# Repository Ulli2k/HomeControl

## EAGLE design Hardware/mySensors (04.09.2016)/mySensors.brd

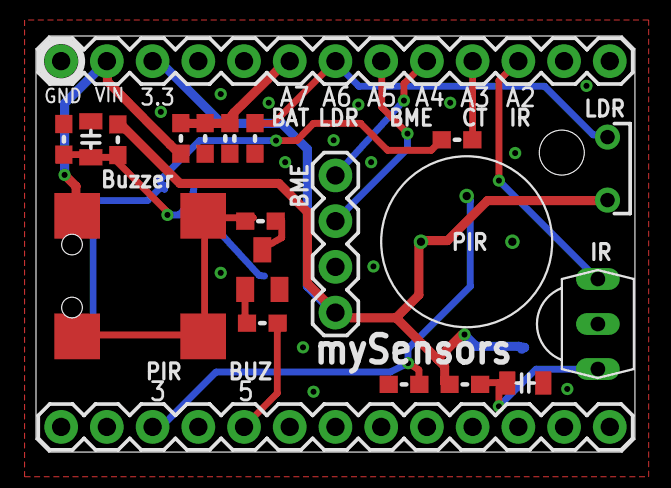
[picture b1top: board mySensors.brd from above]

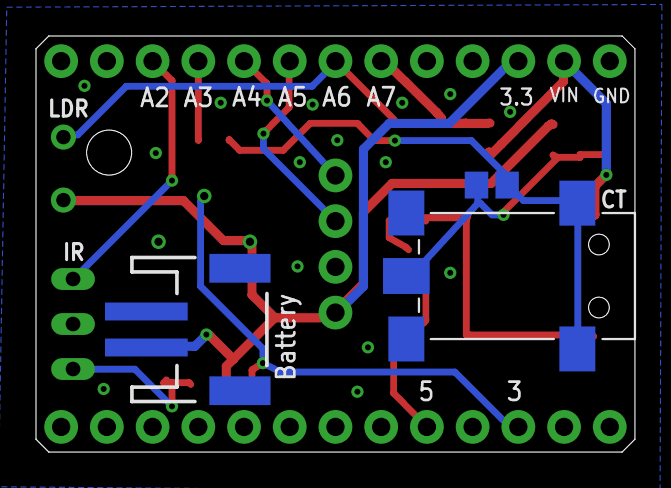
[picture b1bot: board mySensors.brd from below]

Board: 2 copper layers, 33.3 x 23.1 mm, 24 parts (3 on the bottom side), 17 nets.

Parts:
ANALOGSIDE: M13; 1X13
BC817-40: SOT23-BEC
BURDEN: R150 0.1%; R0805
C2: 10u; 0805-CAP
C3: 4,7u; 0805-CAP
C105: 0,1u; 0603-CAP
CT1: 1503_13; 1503-03
DIGITALSIDE: M13; 1X13
IR-RX: TSOP4836; TSOP18XX
J1: JST-2-SMD
JP1: CONNECTORS_M4""; CONNECTORS_1X4
LDR: GL5537; M9960
PIEZO: BUZZER-PIEZO_SMD
R1: 100k; 0603-RES
R2, R5, R104: 470k; 0603-RES
R3: 100; 0603-RES
R4: 33; 0603-RES
R6, R103: 1k; 0603-RES
R7: 1M; 0603-RES
R8: 301k; 0603-RES
U$1: EKMB1X011X; PIR-PANASONIC-VZ-WL-STANDARD

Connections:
+3V3: ANALOGSIDE.11, J1.2, JP1.1, LDR.1, R2.1, R3.2, U$1.VDD
A2_IR-RX: ANALOGSIDE.3, IR-RX.OUT
A3_RFM-3_RST: ANALOGSIDE.4, R6.2
A4_SDA_BME: ANALOGSIDE.5, JP1.4
A5_SCL_BME: ANALOGSIDE.6, JP1.3
A6_LDR: ANALOGSIDE.7, LDR.2, R8.2
A7_BAT-SENS: ANALOGSIDE.8, C105.1, R7.2, R104.1
D3_RFM-2_IRQ: DIGITALSIDE.11, R1.1, U$1.OUT
D5_BUZZER: DIGITALSIDE.9, R103.1
GND: ANALOGSIDE.13, BC817-40.E, C2.2, C3.2, C105.2, IR-RX.GND, J1.1, JP1.2, R1.2, R5.2, R8.1, R104.2, U$1.GND
unnamed: BURDEN.2, C2.1, CT1.1, R2.2, R5.1
unnamed: BURDEN.1, CT1.4, CT1.4-2, R6.1
unnamed: PIEZO.-, PIEZO.DUMMY, PIEZO.DUMMY1, R4.1
unnamed: BC817-40.C, R4.2
unnamed: BC817-40.B, R103.2
unnamed: C3.1, IR-RX.VCC, R3.1
VCC: ANALOGSIDE.12, PIEZO.+, R7.1

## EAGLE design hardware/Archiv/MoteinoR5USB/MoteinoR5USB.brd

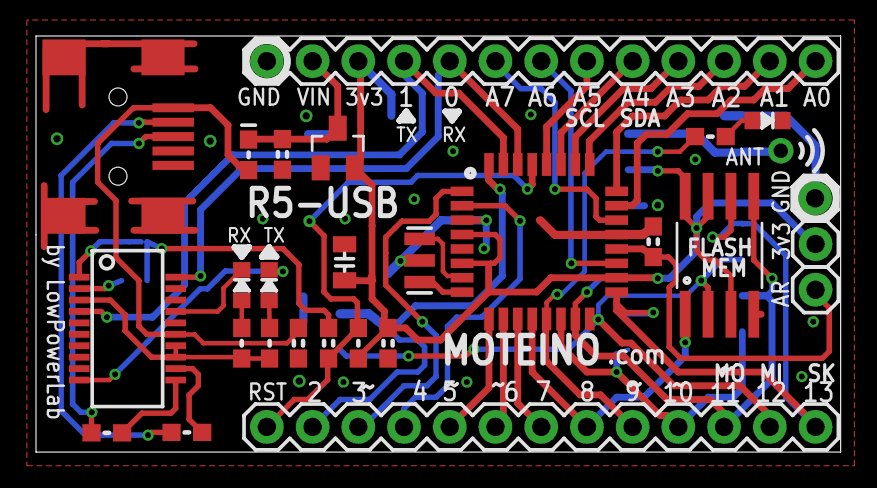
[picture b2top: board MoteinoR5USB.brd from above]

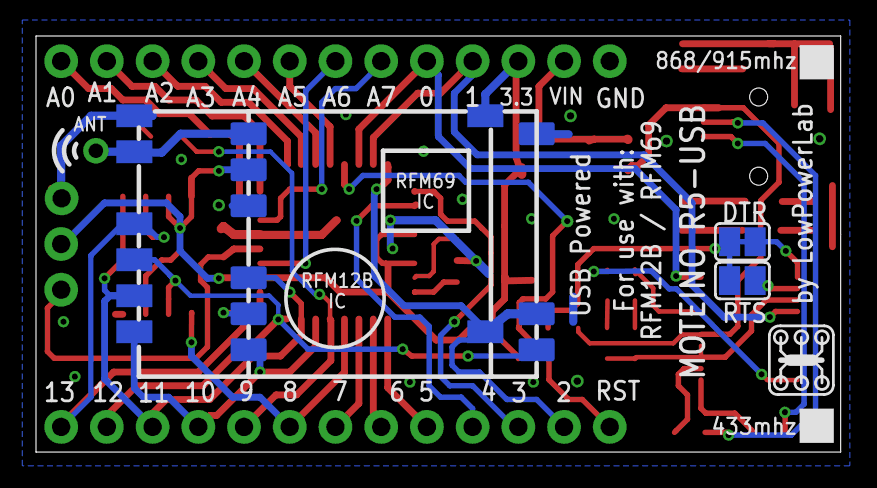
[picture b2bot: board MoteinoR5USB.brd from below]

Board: 2 copper layers, 44.7 x 23.1 mm, 33 parts (5 on the bottom side), 44 nets.

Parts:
+: M01PTH; 1X01
ANALOGSIDE: M13; 1X13
ATMEGA328: ATMega-328; TQFP32-08
C1, C4, C5: 0.1; 0603-CAP
C2: 1u; 0603-CAP
C3: 10u; 0805-CAP
C6: 0.1u; 0603-CAP
CN1: MINIB; USB-MINIB
D: SHOTTKY; 0603-RES
DIGITALSIDE: M13; 1X13
IC3: MCP1703CB; SOT23
JP1, JP2: M01PTH; 1X01
R1: 10k; 0603-RES
R2: 1k5; 0603-RES
R3, R5: 27; 0603-RES
R4, R6: 0603-RES
RFM12B: RFM12B_MINPADS; RFM12B-MINPADS
SJ1, SJ6: SJW
U1: FT231XS; SSOP20_L
U$1: RFM12B_ANTENNA; RFM12B-ANTENNA
U$2, U$4, U$7: LED0603; 0603-LED
U$3: LOGO_LOWPOWERLAB
U$5: RFM69; RFM69W-MINPADS
U$6: AT25F512BWIDE_5.3MM; SO08WIDE
X1: 16 MHz; RESONATOR-SMD

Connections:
A0: ANALOGSIDE.1, ATMEGA328.23
A1: ANALOGSIDE.2, ATMEGA328.24
A2: ANALOGSIDE.3, ATMEGA328.25
A3: ANALOGSIDE.4, ATMEGA328.26
A4_SDA: ANALOGSIDE.5, ATMEGA328.27
A5_SCL: ANALOGSIDE.6, ATMEGA328.28
A6: ANALOGSIDE.7, ATMEGA328.19
A7: ANALOGSIDE.8, ATMEGA328.22
AREF: ATMEGA328.20, C5.1, JP1.1
D0_RX: ANALOGSIDE.9, ATMEGA328.30, U1.20
D1_TX: ANALOGSIDE.10, ATMEGA328.31, U1.4
D2: ATMEGA328.32, DIGITALSIDE.12, RFM12B.IRQ, U$5.DIO0
D3: ATMEGA328.1, DIGITALSIDE.11
D4: ATMEGA328.2, DIGITALSIDE.10
D5: ATMEGA328.9, DIGITALSIDE.9
D6: ATMEGA328.10, DIGITALSIDE.8
D7: ATMEGA328.11, DIGITALSIDE.7
D8: ATMEGA328.12, DIGITALSIDE.6, U$6.1
D9: ATMEGA328.13, DIGITALSIDE.5, R2.2
D10_SS: ATMEGA328.14, DIGITALSIDE.4, RFM12B.SEL, U$5.NSS
D11_MOSI: ATMEGA328.15, DIGITALSIDE.3, RFM12B.SDI, U$5.MOSI, U$6.5
D12_MISO: ATMEGA328.16, DIGITALSIDE.2, RFM12B.SDO, U$5.MISO, U$6.2
D13_SCK: ATMEGA328.17, DIGITALSIDE.1, RFM12B.SCK, U$5.SCK, U$6.6
D+: CN1.D+, R5.1
D-: CN1.D-, R3.1
DTR: SJ6.2, U1.1
FTDI3.3V: R4.2, R6.2, U1.3, U1.13, U1.14
GND: ANALOGSIDE.13, ATMEGA328.3, ATMEGA328.5, ATMEGA328.21, C2.2, C3.2, C4.2, C5.2, C6.2, CN1.GND, IC3.1, JP2.1, RFM12B.GND, U1.6, U1.16, U$2.MINUS, U$5.GND, U$6.4, X1.2
unnamed: ATMEGA328.7, X1.1
unnamed: R2.1, U$2.PLUS
unnamed: RFM12B.ANT, U$1.P$1, U$5.ANA
unnamed: R3.2, U1.12
unnamed: R5.2, U1.11
unnamed: U1.17, U$4.MINUS
unnamed: U1.10, U$7.MINUS
unnamed: R4.1, U$7.PLUS
unnamed: R6.1, U$4.PLUS
unnamed: ATMEGA328.8, X1.3
RST: ATMEGA328.29, C1.1, DIGITALSIDE.13, R1.2
RTS: SJ1.1, U1.2
RTS_OR_DTR: C1.2, SJ1.2, SJ6.1
VBUS: C6.1, CN1.VBUS, D.2, U1.15
VCC: +.1, ANALOGSIDE.11, ATMEGA328.4, ATMEGA328.6, ATMEGA328.18, C3.1, C4.1, IC3.2, R1.1, RFM12B.VDD, U$5.VDD, U$6.3, U$6.7, U$6.8
VIN: ANALOGSIDE.12, C2.1, D.1, IC3.3

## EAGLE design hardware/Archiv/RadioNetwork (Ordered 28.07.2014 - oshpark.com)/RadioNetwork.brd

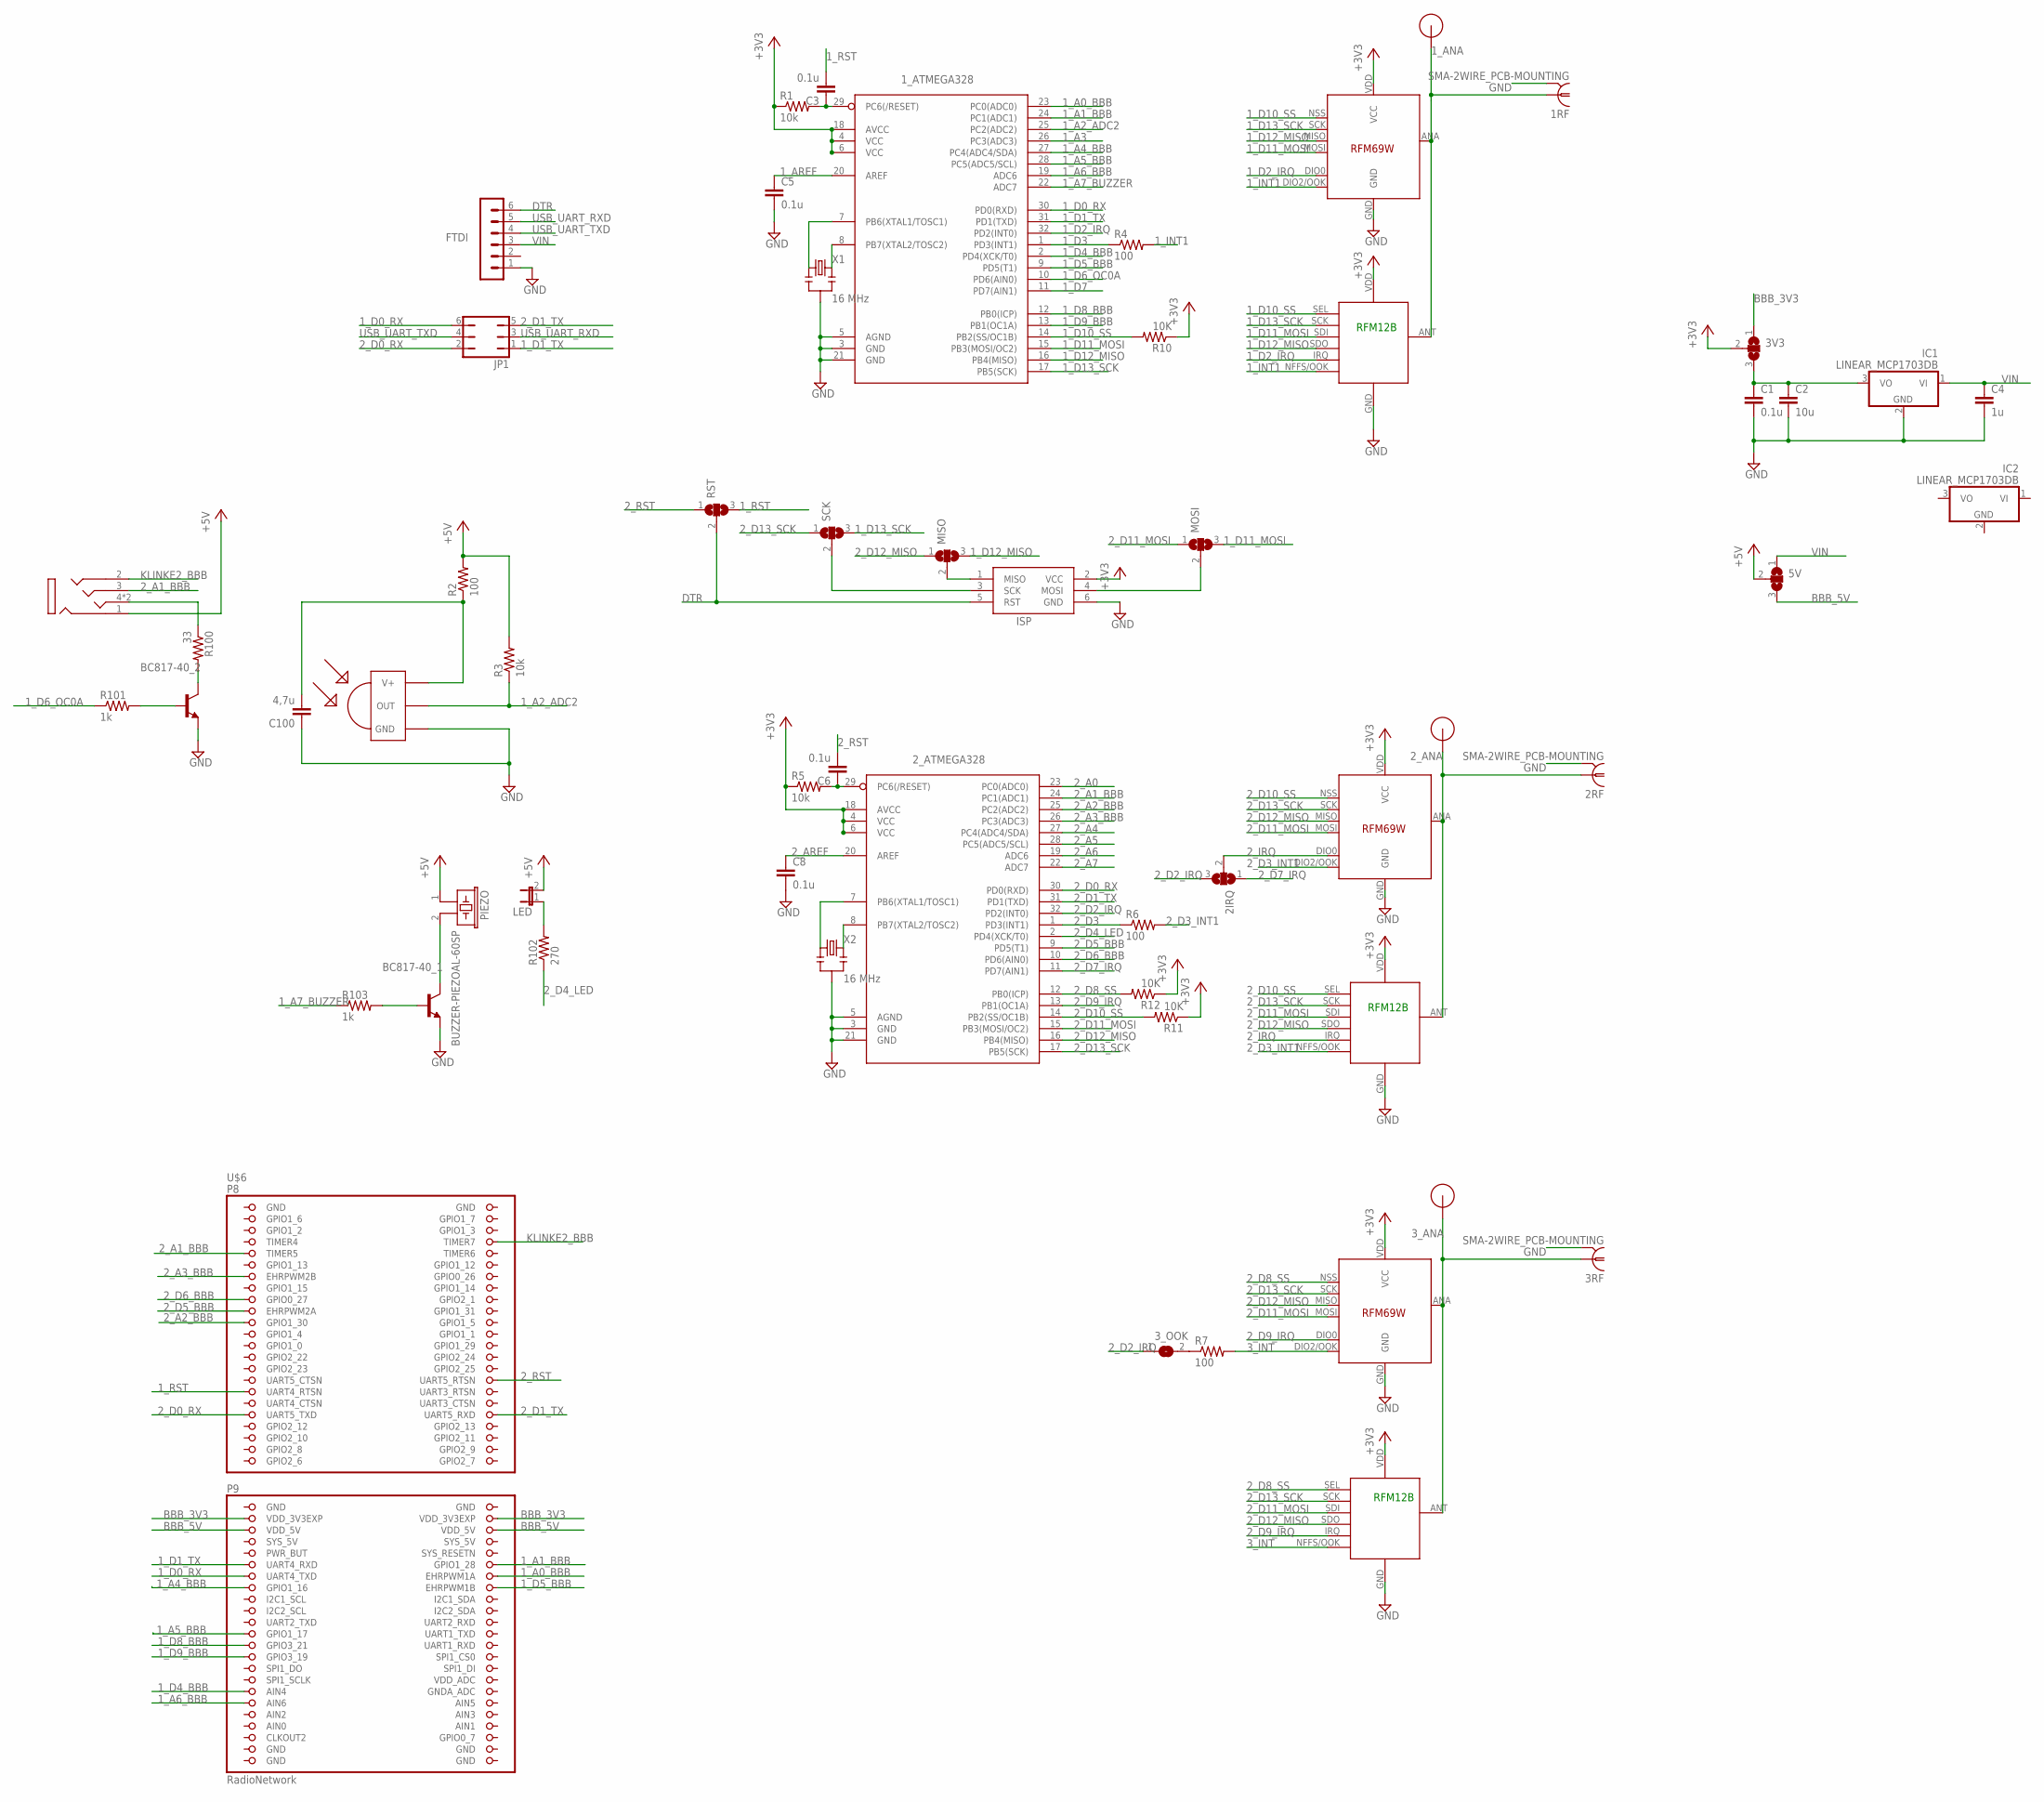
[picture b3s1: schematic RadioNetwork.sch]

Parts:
1RF, 2RF, 3RF: SMA-2WIRE_PCB-MOUNTING; J01151A0931
1_ATMEGA328, 2_ATMEGA328: ATMega-328; TQFP32-08
1_RFM12B, 2_RFM12B, 3_RFM12B: RFM12B_MINPADS; RFM12B-MINPADS
1_RFM69, 2_RFM69, 3_RFM69: RFM69_MINIPADS; RFM69W-MINPADS
2IRQ, 3V3, 5V: SJ2W; SJ_2
3_OOK: SJ
BC817-40_1, BC817-40_2: BC817-40-NPN-SOT23-BEC; SOT23-BEC
C1, C3, C5, C6, C8: 0.1u; 0603-CAP
C2: 10u; 0603-CAP
C4: 1u; 0603-CAP
C100: 4,7u; 0603-CAP
FTDI: FTDI; MA06-1
IC1, IC2: LINEAR_MCP1703DB; LINEAR_SOT223
IR-RX: TSOP4836; TSOP18XX
IR-TX: 1503_13; 1503-03
ISP: AVRISP-6; AVRISP
JP1: JP3Q
LED: JP1E; JP1
MISO: SJ2W; SJ_2
MOSI: SJ2W; SJ_2
PIEZO: BUZZER-PIEZOAL-60SP; AL-60SP05
R1, R3, R5: 10k; 0603-RES
R2, R4, R6, R7: 100; 0603-RES
R10, R11, R12: 10K; 0603-RES
R100: 33; 0603-RES
R101, R103: 1k; 0603-RES
R102: 270; 0603-RES
RST: SJ2W; SJ_2
SCK: SJ2W; SJ_2
U$1, U$2, U$5: RFM12B_ANTENNA; RFM12B-ANTENNA
U$6: RadioNetwork; BEAGLEBONE_SHIELD
X1, X2: 16 MHz; RESONATOR-SMD

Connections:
1_A0_BBB: 1_ATMEGA328.23 (PC0(ADC0)), U$6.60 (EHRPWM1A)
1_A1_BBB: 1_ATMEGA328.24 (PC1(ADC1)), U$6.58 (GPIO1_28)
1_A2_ADC2: 1_ATMEGA328.25 (PC2(ADC2)), IR-RX.OUT, R3.1
1_A3: 1_ATMEGA328.26 (PC3(ADC3))
1_A4_BBB: 1_ATMEGA328.27 (PC4(ADC4/SDA)), U$6.61 (GPIO1_16)
1_A5_BBB: 1_ATMEGA328.28 (PC5(ADC5/SCL)), U$6.69 (GPIO1_17)
1_A6_BBB: 1_ATMEGA328.19 (ADC6), U$6.81 (AIN6)
1_A7_BUZZER: 1_ATMEGA328.22 (ADC7), R103.1
1_ANA: 1RF.1, 1_RFM12B.ANT, 1_RFM69.ANA (ANT), U$1.P$1
1_AREF: 1_ATMEGA328.20 (AREF), C5.1
1_D0_RX: 1_ATMEGA328.30 (PD0(RXD)), JP1.6, U$6.59 (UART4_TXD)
1_D1_TX: 1_ATMEGA328.31 (PD1(TXD)), JP1.1, U$6.57 (UART4_RXD)
1_D2_IRQ: 1_ATMEGA328.32 (PD2(INT0)), 1_RFM12B.IRQ, 1_RFM69.DIO0 (DIO0/IRQ)
1_D3: 1_ATMEGA328.1 (PD3(INT1)), R4.1
1_D4_BBB: 1_ATMEGA328.2 (PD4(XCK/T0)), U$6.79 (AIN4)
1_D5_BBB: 1_ATMEGA328.9 (PD5(T1)), U$6.62 (EHRPWM1B)
1_D6_OC0A: 1_ATMEGA328.10 (PD6(AIN0)), R101.1
1_D7: 1_ATMEGA328.11 (PD7(AIN1))
1_D8_BBB: 1_ATMEGA328.12 (PB0(ICP)), U$6.71 (GPIO3_21)
1_D9_BBB: 1_ATMEGA328.13 (PB1(OC1A)), U$6.73 (GPIO3_19)
1_D10_SS: 1_ATMEGA328.14 (PB2(SS/OC1B)), 1_RFM12B.SEL, 1_RFM69.NSS (SEL), R10.2
1_D11_MOSI: 1_ATMEGA328.15 (PB3(MOSI/OC2)), 1_RFM12B.SDI (SDI/MOSI), 1_RFM69.MOSI, MOSI.3
1_D12_MISO: 1_ATMEGA328.16 (PB4(MISO)), 1_RFM12B.SDO (SDO/MISO), 1_RFM69.MISO, MISO.3
1_D13_SCK: 1_ATMEGA328.17 (PB5(SCK)), 1_RFM12B.SCK, 1_RFM69.SCK, SCK.3
1_INT1: 1_RFM12B.NFFS/OOK, 1_RFM69.DIO2/OOK, R4.2
1_RST: C3.2, RST.3, U$6.33 (UART4_RTSN)
2_A0: 2_ATMEGA328.23 (PC0(ADC0))
2_A1_BBB: 2_ATMEGA328.24 (PC1(ADC1)), IR-TX.3, U$6.9 (TIMER5)
2_A2_BBB: 2_ATMEGA328.25 (PC2(ADC2)), U$6.21 (GPIO1_30)
2_A3_BBB: 2_ATMEGA328.26 (PC3(ADC3)), U$6.13 (EHRPWM2B)
2_A4: 2_ATMEGA328.27 (PC4(ADC4/SDA))
2_A5: 2_ATMEGA328.28 (PC5(ADC5/SCL))
2_A6: 2_ATMEGA328.19 (ADC6)
2_A7: 2_ATMEGA328.22 (ADC7)
2_ANA: 2RF.1, 2_RFM12B.ANT, 2_RFM69.ANA (ANT), U$5.P$1
2_AREF: 2_ATMEGA328.20 (AREF), C8.1
2_D0_RX: 2_ATMEGA328.30 (PD0(RXD)), JP1.2, U$6.37 (UART5_TXD)
2_D1_TX: 2_ATMEGA328.31 (PD1(TXD)), JP1.5, U$6.38 (UART5_RXD)
2_D2_IRQ: 2IRQ.3, 2_ATMEGA328.32 (PD2(INT0)), 3_OOK.1
2_D3: 2_ATMEGA328.1 (PD3(INT1)), R6.1
2_D3_INT1: 2_RFM12B.NFFS/OOK, 2_RFM69.DIO2/OOK, R6.2
2_D4_LED: 2_ATMEGA328.2 (PD4(XCK/T0)), R102.1
2_D5_BBB: 2_ATMEGA328.9 (PD5(T1)), U$6.19 (EHRPWM2A)
2_D6_BBB: 2_ATMEGA328.10 (PD6(AIN0)), U$6.17 (GPIO0_27)
2_D7_IRQ: 2IRQ.1, 2_ATMEGA328.11 (PD7(AIN1))
2_D8_SS: 2_ATMEGA328.12 (PB0(ICP)), 3_RFM12B.SEL, 3_RFM69.NSS (SEL), R12.2
2_D9_IRQ: 2_ATMEGA328.13 (PB1(OC1A)), 3_RFM12B.IRQ, 3_RFM69.DIO0 (DIO0/IRQ)
2_D10_SS: 2_ATMEGA328.14 (PB2(SS/OC1B)), 2_RFM12B.SEL, 2_RFM69.NSS (SEL), R11.2
2_D11_MOSI: 2_ATMEGA328.15 (PB3(MOSI/OC2)), 2_RFM12B.SDI (SDI/MOSI), 2_RFM69.MOSI, 3_RFM12B.SDI (SDI/MOSI), 3_RFM69.MOSI, MOSI.1
2_D12_MISO: 2_ATMEGA328.16 (PB4(MISO)), 2_RFM12B.SDO (SDO/MISO), 2_RFM69.MISO, 3_RFM12B.SDO (SDO/MISO), 3_RFM69.MISO, MISO.1
2_D13_SCK: 2_ATMEGA328.17 (PB5(SCK)), 2_RFM12B.SCK, 2_RFM69.SCK, 3_RFM12B.SCK, 3_RFM69.SCK, SCK.1
2_IRQ: 2IRQ.2, 2_RFM12B.IRQ, 2_RFM69.DIO0 (DIO0/IRQ)
2_RST: C6.2, RST.1, U$6.32 (UART5_RTSN)
3_ANA: 3RF.1, 3_RFM12B.ANT, 3_RFM69.ANA (ANT), U$2.P$1
3_INT: 3_RFM12B.NFFS/OOK, 3_RFM69.DIO2/OOK, R7.2
+3V3: 1_ATMEGA328.4 (VCC), 1_ATMEGA328.6 (VCC), 1_ATMEGA328.18 (AVCC), 1_RFM12B.VDD, 1_RFM69.VDD (VCC), 2_ATMEGA328.4 (VCC), 2_ATMEGA328.6 (VCC), 2_ATMEGA328.18 (AVCC), 2_RFM12B.VDD, 2_RFM69.VDD (VCC), 3V3.2, 3_RFM12B.VDD, 3_RFM69.VDD (VCC), ISP.2 (VCC), R1.1, R5.1, R10.1, R11.1, R12.1
+5V: 5V.2, IR-TX.1, LED.2, PIEZO.1, R2.2, R3.2
AIN0: U$6.85 (AIN0)
BBB_3V3: 3V3.1, U$6.49 (VDD_3V3EXP), U$6.50 (VDD_3V3EXP)
BBB_5V: 5V.3, U$6.51 (VDD_5V), U$6.52 (VDD_5V)
DTR: FTDI.6, ISP.5 (RST), RST.2
GND: 1RF.G@1 (2), 1RF.G@2 (2), 1RF.G@3 (2), 1RF.G@4 (2), 1_ATMEGA328.3 (GND), 1_ATMEGA328.5 (AGND), 1_ATMEGA328.21 (GND), 1_RFM12B.GND, 1_RFM69.GND, 2RF.G@1 (2), 2RF.G@2 (2), 2RF.G@3 (2), 2RF.G@4 (2), 2_ATMEGA328.3 (GND), 2_ATMEGA328.5 (AGND), 2_ATMEGA328.21 (GND), 2_RFM12B.GND, 2_RFM69.GND, 3RF.G@1 (2), 3RF.G@2 (2), 3RF.G@3 (2), 3RF.G@4 (2), 3_RFM12B.GND, 3_RFM69.GND, BC817-40_1.E, BC817-40_2.E, C1.2, C2.2, C4.2, C5.2, C8.2, C100.1, FTDI.1, IC1.2 (GND), IR-RX.GND, ISP.6 (GND), U$6.1 (GND), U$6.2 (GND), U$6.47 (GND), U$6.48 (GND), U$6.89 (GND), U$6.90 (GND), U$6.91 (GND), U$6.92 (GND), X1.2, X2.2
KLINKE2_BBB: IR-TX.2, U$6.8 (TIMER7)
unnamed: 1_ATMEGA328.7 (PB6(XTAL1/TOSC1)), X1.1
unnamed: 3V3.3, C1.1, C2.1, IC1.3 (VO)
unnamed: 2_ATMEGA328.7 (PB6(XTAL1/TOSC1)), X2.1
unnamed: BC817-40_2.C, R100.2
unnamed: 2_ATMEGA328.8 (PB7(XTAL2/TOSC2)), X2.3
unnamed: 2_ATMEGA328.29 (PC6(/RESET)), C6.1, R5.2
unnamed: 3_OOK.2, R7.1
unnamed: BC817-40_1.C, PIEZO.2
unnamed: 1_ATMEGA328.29 (PC6(/RESET)), C3.1, R1.2
unnamed: BC817-40_1.B, R103.2
unnamed: C100.2, IR-RX.VCC (V+), R2.1
unnamed: IR-TX.4, IR-TX.4-2 (4), R100.1
unnamed: BC817-40_2.B, R101.2
unnamed: 1_ATMEGA328.8 (PB7(XTAL2/TOSC2)), X1.3
unnamed: LED.1, R102.2
unnamed: ISP.1 (MISO), MISO.2
unnamed: ISP.4 (MOSI), MOSI.2
unnamed: ISP.3 (SCK), SCK.2
SYS_5V: U$6.53 (SYS_5V)
USB_UART_RXD: FTDI.5, JP1.3
USB_UART_TXD: FTDI.4, JP1.4
VIN: 5V.1, C4.1, FTDI.3, IC1.1 (VI)

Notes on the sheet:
RFM12B

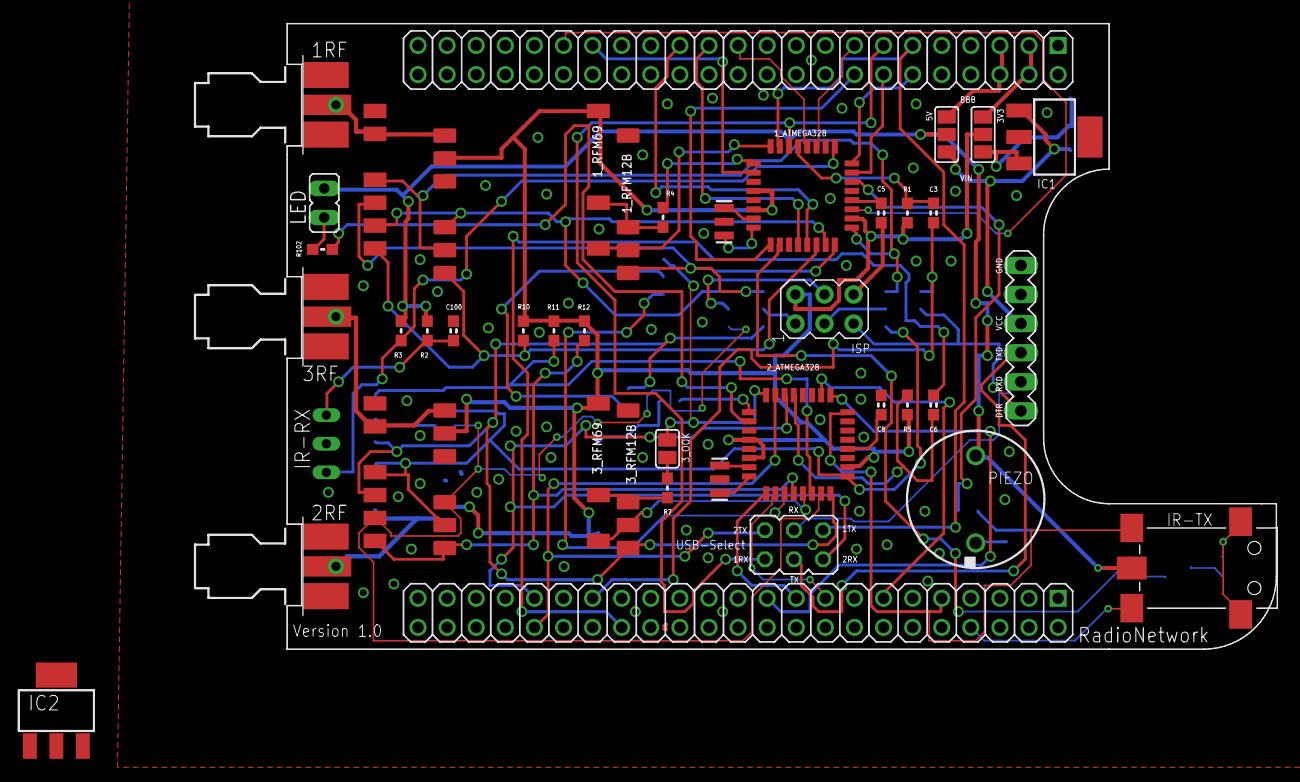
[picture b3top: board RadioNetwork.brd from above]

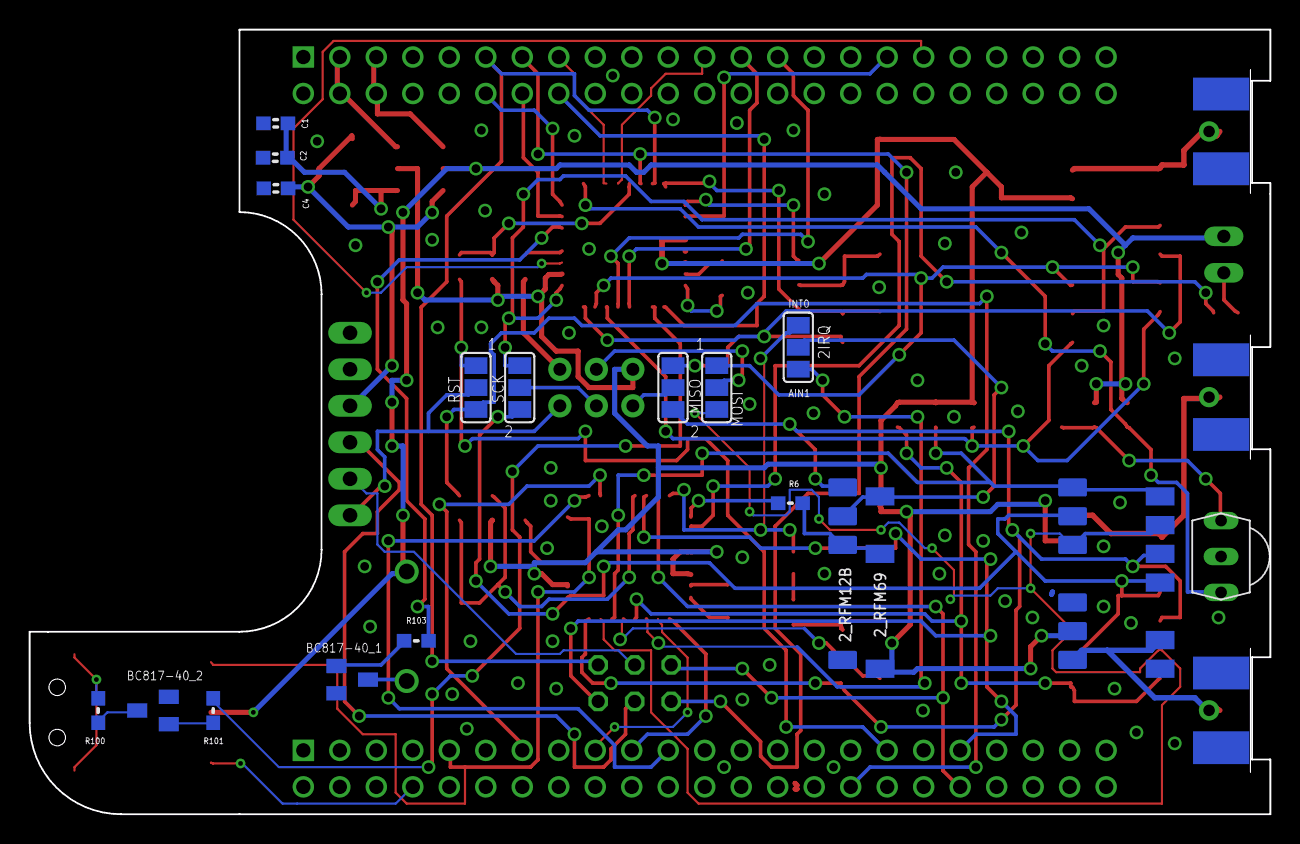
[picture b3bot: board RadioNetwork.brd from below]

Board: 2 copper layers, 86.4 x 54.6 mm, 58 parts (17 on the bottom side), 76 nets.

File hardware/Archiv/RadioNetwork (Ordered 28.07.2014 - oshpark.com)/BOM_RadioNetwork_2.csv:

"Part";"Value";"Device";"Package";"Description";"BUERKLIN";"CONRAD";"MF";"MPN";"OC_FARNELL";"OC_NEWARK";
"1RF";"SMA-2WIRE_PCB-MOUNTING";"SMA-2WIRE_PCB-MOUNTING";"J01151A0931";"SMA 50 Ohm Straight Jack Receptacle - PCB Mountung";"76F410";"";"";"";"";"";
"1_ATMEGA328";"ATMega-328";"ATMEGA168/328TQFP32";"TQFP32-08";"Atmel 32-pin 8-bit micro, 16k flash.";"64 S 3046";"";"";"";"";"";
"1_RFM12B";"RFM12B_MINPADS";"RFM12B_MINPADS";"RFM12B-MINPADS";"";"";"";"";"";"";"";
"1_RFM69";"RFM69_MINIPADS";"RFM69_MINIPADS";"RFM69W-MINPADS";"";"";"";"";"";"";"";
"2IRQ";"";"SJ2W";"SJ_2";"SMD solder JUMPER";"";"";"";"";"";"";
"2RF";"SMA-2WIRE_PCB-MOUNTING";"SMA-2WIRE_PCB-MOUNTING";"J01151A0931";"SMA 50 Ohm Straight Jack Receptacle - PCB Mountung";"76F410";"";"";"";"";"";
"2_ATMEGA328";"ATMega-328";"ATMEGA168/328TQFP32";"TQFP32-08";"Atmel 32-pin 8-bit micro, 16k flash.";"64 S 3046";"";"";"";"";"";
"2_RFM12B";"RFM12B_MINPADS";"RFM12B_MINPADS";"RFM12B-MINPADS";"";"";"";"";"";"";"";
"2_RFM69";"RFM69_MINIPADS";"RFM69_MINIPADS";"RFM69W-MINPADS";"";"";"";"";"";"";"";
"3RF";"SMA-2WIRE_PCB-MOUNTING";"SMA-2WIRE_PCB-MOUNTING";"J01151A0931";"SMA 50 Ohm Straight Jack Receptacle - PCB Mountung";"76F410";"";"";"";"";"";
"3V3";"";"SJ2W";"SJ_2";"SMD solder JUMPER";"";"";"";"";"";"";
"3_OOK";"";"SJ";"SJ";"SMD solder JUMPER";"";"";"";"";"";"";
"3_RFM12B";"RFM12B_MINPADS";"RFM12B_MINPADS";"RFM12B-MINPADS";"";"";"";"";"";"";"";
"3_RFM69";"RFM69_MINIPADS";"RFM69_MINIPADS";"RFM69W-MINPADS";"";"";"";"";"";"";"";
"5V";"";"SJ2W";"SJ_2";"SMD solder JUMPER";"";"";"";"";"";"";
"BC817-40_1";"";"BC817-40-NPN-SOT23-BEC";"SOT23-BEC";"NPN Transistror";"12S6220";"";"";"";"";"";
"BC817-40_2";"";"BC817-40-NPN-SOT23-BEC";"SOT23-BEC";"NPN Transistror";"12S6220";"";"";"";"";"";
"C1";"0.1u";"CAP0603-CAP";"0603-CAP";"Capacitor";"53 D 1726";"";"";"";"";"";
"C2";"10u";"CAP0603-CAP";"0603-CAP";"Capacitor";"53 D 1652";"";"";"";"";"";
"C3";"0.1u";"CAP0603-CAP";"0603-CAP";"Capacitor";"53 D 1726";"";"";"";"";"";
"C4";"1u";"CAP0603-CAP";"0603-CAP";"Capacitor";"53 D 1657";"";"";"";"";"";
"C5";"0.1u";"CAP0603-CAP";"0603-CAP";"Capacitor";"53 D 1726";"";"";"";"";"";
"C6";"0.1u";"CAP0603-CAP";"0603-CAP";"Capacitor";"53 D 1726";"";"";"";"";"";
"C8";"0.1u";"CAP0603-CAP";"0603-CAP";"Capacitor";"53 D 1726";"";"";"";"";"";
"C100";"4,7u";"CAP0603-CAP";"0603-CAP";"Capacitor";"53 D 1659";"";"";"";"";"";
"FTDI";"FTDI";"MA06-1";"MA06-1";"PIN HEADER";"59 F 2134";"";"";"";"";"";
"IC1";"LINEAR_MCP1703DB";"LINEAR_MCP1703DB";"LINEAR_SOT223";"250 mA, 16V, Low Quiescent Current LDO Regulator";"41 S 7654";"";"";"";"";"";
"IR-RX";"TSOP4836";"TSOP4836";"TSOP18XX";"IR Receiver and Demodulator";"";"171107-62";"";"";"";"";
"IR-TX";"1503_13";"1503_13";"1503-03";"";"39F1215";"";"";"";"";"";
"ISP";"AVRISP-6";"AVRISP-6";"AVRISP";"AVR ISP HEADER";"";"737480 - 62";"";"";"";"";
"JP1";"";"JP3Q";"JP3Q";"JUMPER";"";"737480 - 62";"";"";"";"";
"LED";"";"JP1E";"JP1";"JUMPER";"";"";"";"";"";"";
"MISO";"";"SJ2W";"SJ_2";"SMD solder JUMPER";"";"";"";"";"";"";
"MOSI";"";"SJ2W";"SJ_2";"SMD solder JUMPER";"";"";"";"";"";"";
"PIEZO";"BUZZER-PIEZOAL-60SP";"BUZZER-PIEZOAL-60SP";"AL-60SP05";"Piezoelectric Acoustic Transducer";"";"751553 - 62";"";"";"unknown";"unknown";
"R1";"10k";"RESISTOR0603-RES";"0603-RES";"Resistor";"26 E 816";"";"";"";"";"";
"R2";"100";"RESISTOR0603-RES";"0603-RES";"Resistor";"26 E 768";"";"";"";"";"";
"R3";"10k";"RESISTOR0603-RES";"0603-RES";"Resistor";"26 E 816";"";"";"";"";"";
"R4";"100";"RESISTOR0603-RES";"0603-RES";"Resistor";"26 E 768";"";"";"";"";"";
"R5";"10k";"RESISTOR0603-RES";"0603-RES";"Resistor";"26 E 816";"";"";"";"";"";
"R6";"100";"RESISTOR0603-RES";"0603-RES";"Resistor";"26 E 768";"";"";"";"";"";
"R7";"100";"RESISTOR0603-RES";"0603-RES";"Resistor";"26 E 768";"";"";"";"";"";
"R10";"10K";"RESISTOR0603-RES";"0603-RES";"Resistor";"26 E 816";"";"";"";"";"";
"R11";"10K";"RESISTOR0603-RES";"0603-RES";"Resistor";"26 E 816";"";"";"";"";"";
"R12";"10K";"RESISTOR0603-RES";"0603-RES";"Resistor";"26 E 816";"";"";"";"";"";
"R100";"33";"RESISTOR0603-RES";"0603-RES";"Resistor";"26 E 756";"";"";"";"";"";
"R101";"1k";"RESISTOR0603-RES";"0603-RES";"Resistor";"26 E 792";"";"";"";"";"";
"R102";"270";"RESISTOR0603-RES";"0603-RES";"Resistor";"26 E 778";"";"";"";"";"";
"R103";"1k";"RESISTOR0603-RES";"0603-RES";"Resistor";"26 E 792";"";"";"";"";"";
"RST";"";"SJ2W";"SJ_2";"SMD solder JUMPER";"";"";"";"";"";"";
"SCK";"";"SJ2W";"SJ_2";"SMD solder JUMPER";"";"";"";"";"";"";
"U$1";"RFM12B_ANTENNA";"RFM12B_ANTENNA";"RFM12B-ANTENNA";"";"";"";"";"";"";"";
"U$2";"RFM12B_ANTENNA";"RFM12B_ANTENNA";"RFM12B-ANTENNA";"";"";"";"";"";"";"";
"U$5";"RFM12B_ANTENNA";"RFM12B_ANTENNA";"RFM12B-ANTENNA";"";"";"";"";"";"";"";
"U$6";"RadioNetwork";"BEAGLEBONE_OUTLINE";"BEAGLEBONE_SHIELD";"Should match A3 pinout - but not completely tested";"";"393509 - 62";"";"";"";"";
"X1";"16 MHz";"RESONATORSMD";"RESONATOR-SMD";"Resonator";"";"";"";"";"";"";
"X2";"16 MHz";"RESONATORSMD";"RESONATOR-SMD";"Resonator";"";"";"";"";"";"";

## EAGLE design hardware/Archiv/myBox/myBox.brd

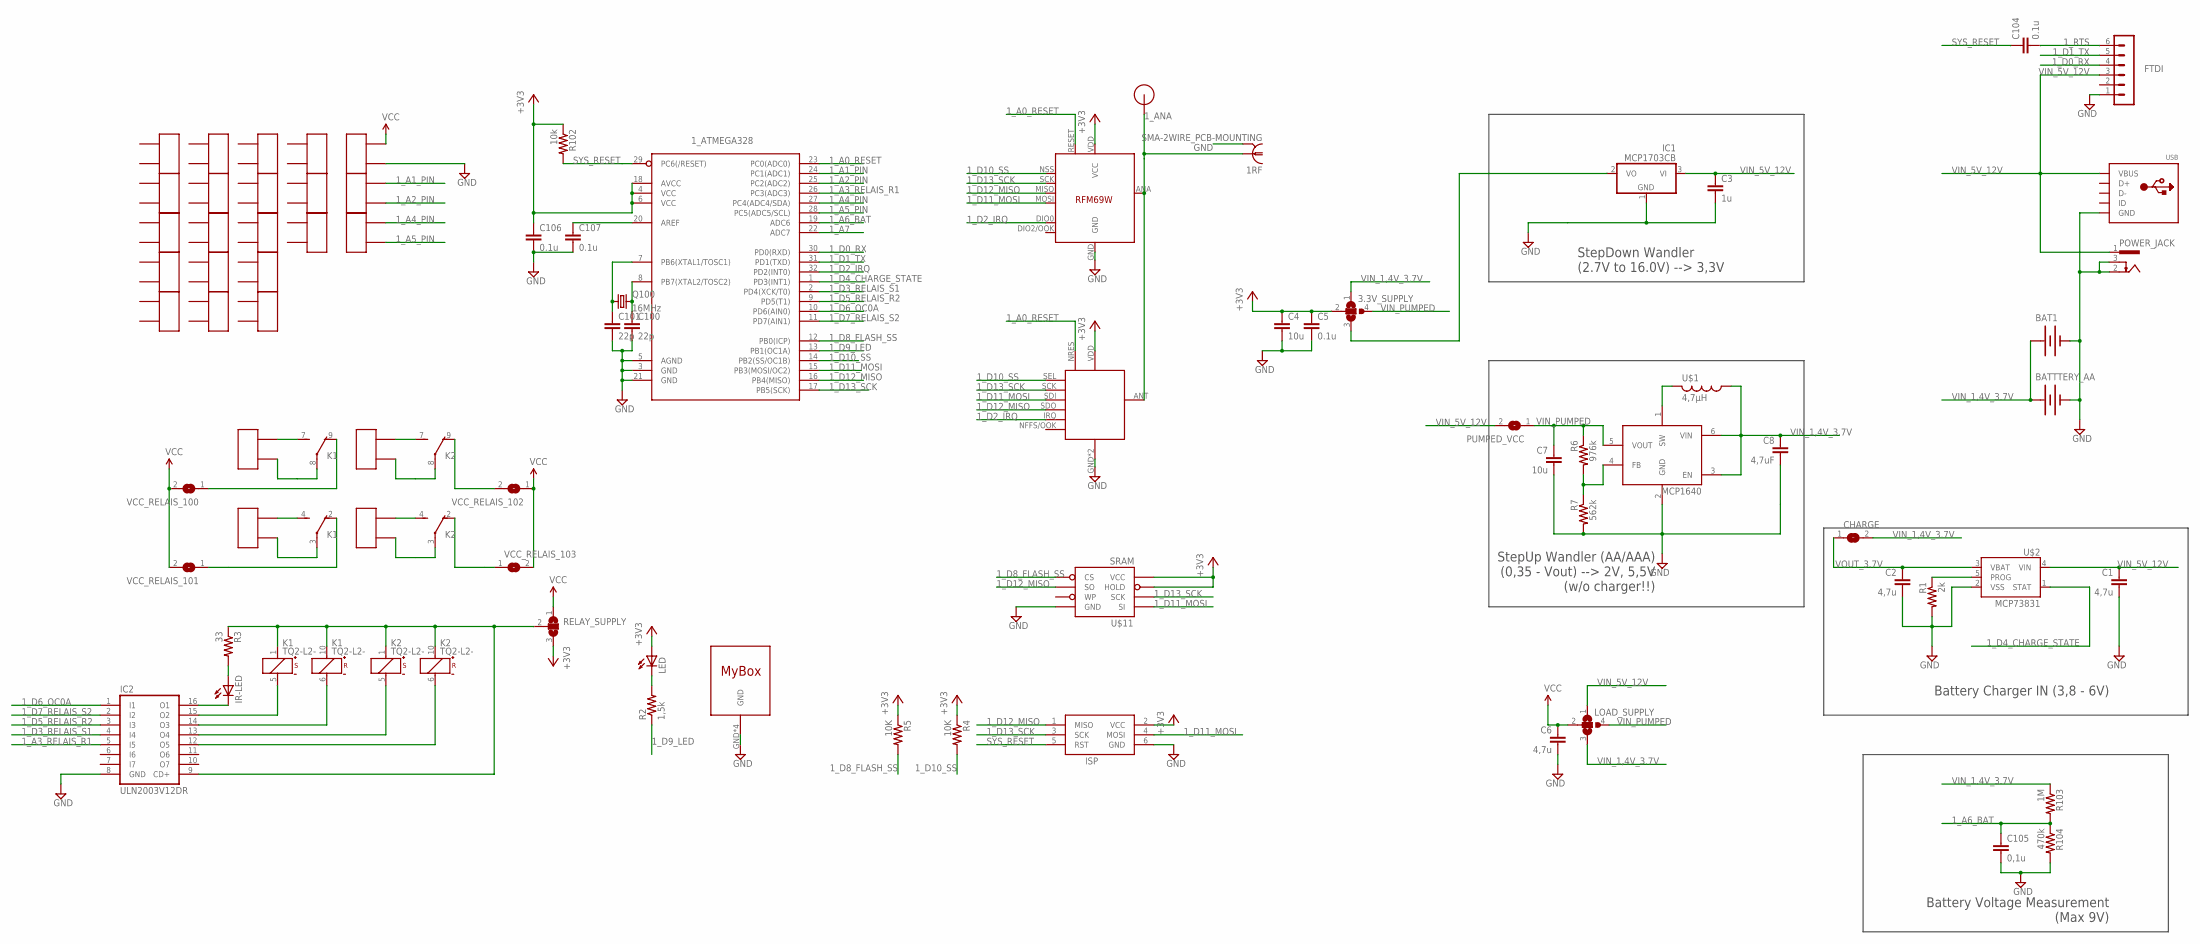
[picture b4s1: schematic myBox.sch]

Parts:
1RF: SMA-2WIRE_PCB-MOUNTING; J01151A0931
1_ATMEGA328: ATMega-328; TQFP32-08
1_RFM12: RFM12B_MINPADS; RFM12B-MINPADS
1_RFM69: RFM69_MINIPADS; RFM69W-MINPADS
3.3V_SUPPLY: SJ3W; SJ_3
ADC1, ADC2: HDR_2PIN; 1X02_NS
BAT1: BATTERY; BATTERY-CR2
BATTTERY_AA: BATTERYAA; BATTERY-AA
C1, C2, C6: 4,7u; 0603-CAP
C3: 1u; 0603-CAP
C4, C7: 10u; 0603-CAP
C5, C104, C106, C107: 0.1u; 0603-CAP
C8: 4,7uF; 0603-CAP
C100, C101: 22p; 0603-CAP
C105: 0,1u; 0603-CAP
CHARGE: SJ
FTDI: FTDI; MA06-1
IC1: MCP1703CB; SOT23
IC2: ULN2003V12DR; SO16
IR-LED: LED5MM
IR/RELAY_SATELLITE: MY-BOX
ISP: AVRISP; AVRISP-EDGE
K1, K2: TQ2-L2-; TQ2; MPN TQ2-L2-3V
LED: LED3MM
LOAD_SUPPLY: SJ3W; SJ_3
POWER_JACK: LUMBERG_1613-200-62; 733980-62
PUMPED_VCC: SJ
Q100: 16MHz; HC49/S
R1: 2k; 0603-RES
R2: 1,5k; 0603-RES
R3: 33; 0603-RES
R4, R5: 10K; 0603-RES
R6: 976k; 0603-RES
R7: 562k; 0603-RES
R102: 10k; 0603-RES
R103: 1M; 0603-RES
R104: 470k; 0603-RES
RELAY_SUPPLY: SJ2W; SJ_2
U1: MCP1640; SOT23-6
U$1: 4,7µH; INDUCTOR_EPCOS
U$2: MCP73831; SOT23-5
U$3, U$4, U$5, U$6, U$7, U$8, U$9, U$10, U$12, U$13, U$14, U$15, U$16, U$17, U$19, U$20, U$21, U$22, U$23, U$24, U$25, U$26: HDR_2PIN; 1X02_NS
U$11: SRAM; LOWPOWERLAB_SO08
U$18: RFM12B_ANTENNA; RFM12B-ANTENNA
USB: USBMINIB; USB-MINIB
VCC: HDR_2PIN; 1X02_NS
VCC_RELAIS_100, VCC_RELAIS_101, VCC_RELAIS_102, VCC_RELAIS_103: SJ

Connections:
1_A0_RESET: 1_ATMEGA328.23 (PC0(ADC0)), 1_RFM12.NRES, 1_RFM69.RESET
1_A1_PIN: 1_ATMEGA328.24 (PC1(ADC1)), ADC1.1
1_A2_PIN: 1_ATMEGA328.25 (PC2(ADC2)), ADC1.2
1_A3_RELAIS_R1: 1_ATMEGA328.26 (PC3(ADC3)), IC2.5 (I5)
1_A4_PIN: 1_ATMEGA328.27 (PC4(ADC4/SDA)), ADC2.1
1_A5_PIN: 1_ATMEGA328.28 (PC5(ADC5/SCL)), ADC2.2
1_A6_BAT: 1_ATMEGA328.19 (ADC6), C105.1, R103.2, R104.1
1_A7: 1_ATMEGA328.22 (ADC7)
1_ANA: 1RF.1, 1_RFM12.ANT, 1_RFM69.ANA (ANT), U$18.P$1
1_AREF: 1_ATMEGA328.20 (AREF), C107.1
1_D0_RX: 1_ATMEGA328.30 (PD0(RXD)), FTDI.4
1_D1_TX: 1_ATMEGA328.31 (PD1(TXD)), FTDI.5
1_D2_IRQ: 1_ATMEGA328.32 (PD2(INT0)), 1_RFM12.IRQ, 1_RFM69.DIO0 (DIO0/IRQ)
1_D3_RELAIS_S1: 1_ATMEGA328.2 (PD4(XCK/T0)), IC2.4 (I4)
1_D4_CHARGE_STATE: 1_ATMEGA328.1 (PD3(INT1)), U$2.1 (STAT)
1_D5_RELAIS_R2: 1_ATMEGA328.9 (PD5(T1)), IC2.3 (I3)
1_D6_OC0A: 1_ATMEGA328.10 (PD6(AIN0)), IC2.1 (I1)
1_D7_RELAIS_S2: 1_ATMEGA328.11 (PD7(AIN1)), IC2.2 (I2)
1_D8_FLASH_SS: 1_ATMEGA328.12 (PB0(ICP)), R5.2, U$11.1_CS (CS)
1_D9_LED: 1_ATMEGA328.13 (PB1(OC1A)), R2.1
1_D10_SS: 1_ATMEGA328.14 (PB2(SS/OC1B)), 1_RFM12.SEL, 1_RFM69.NSS (SEL), R4.2
1_D11_MOSI: 1_ATMEGA328.15 (PB3(MOSI/OC2)), 1_RFM12.SDI (SDI/MOSI), 1_RFM69.MOSI, ISP.4 (MOSI), U$11.5_SI (SI)
1_D12_MISO: 1_ATMEGA328.16 (PB4(MISO)), 1_RFM12.SDO (SDO/MISO), 1_RFM69.MISO, ISP.1 (MISO), U$11.2_SO (SO)
1_D13_SCK: 1_ATMEGA328.17 (PB5(SCK)), 1_RFM12.SCK, 1_RFM69.SCK, ISP.3 (SCK), U$11.6_SCK (SCK)
1_RTS: C104.2, FTDI.6
+3V3: 1_ATMEGA328.4 (VCC), 1_ATMEGA328.6 (VCC), 1_ATMEGA328.18 (AVCC), 1_RFM12.VDD, 1_RFM69.VDD (VCC), 3.3V_SUPPLY.2, C4.1, C5.1, C106.1, ISP.2 (VCC), LED.A, R4.1, R5.1, R102.1, RELAY_SUPPLY.3, U$11.7_HOLD (HOLD), U$11.8_VCC (VCC)
GND: 1RF.G@1 (2), 1RF.G@2 (2), 1RF.G@3 (2), 1RF.G@4 (2), 1_ATMEGA328.3 (GND), 1_ATMEGA328.5 (AGND), 1_ATMEGA328.21 (GND), 1_RFM12.GND, 1_RFM12.GND1 (GND), 1_RFM69.GND, BAT1.GND@1 (-), BATTTERY_AA.GND@1 (-), C1.2, C2.2, C3.2, C4.2, C5.2, C6.2, C7.2, C8.2, C100.2, C101.2, C105.2, C106.2, C107.2, FTDI.1, IC1.1 (GND), IC2.8 (GND), IR/RELAY_SATELLITE.GND, IR/RELAY_SATELLITE.GND1, IR/RELAY_SATELLITE.GND2, IR/RELAY_SATELLITE.GND3, ISP.6 (GND), POWER_JACK.2, POWER_JACK.3, R1.2, R7.2, R104.2, U1.2 (GND), U$2.2 (VSS), U$11.4_GND (GND), USB.GND, VCC.2
unnamed: 1_ATMEGA328.7 (PB6(XTAL1/TOSC1)), C101.1, Q100.1
unnamed: R1.1, U$2.5 (PROG)
unnamed: IR-LED.A, R3.2
unnamed: IC2.16 (O1), IR-LED.K (C)
unnamed: IC2.15 (O2), K1.5 (-)
unnamed: IC2.14 (O3), K1.6 (-)
unnamed: 1_ATMEGA328.8 (PB7(XTAL2/TOSC2)), C100.1, Q100.2
unnamed: 3.3V_SUPPLY.3, IC1.2 (VO)
unnamed: K2.3, U$24.1
unnamed: K1.4 (S), U$22.2
unnamed: K1.8, U$21.1
unnamed: K1.7 (S), U$21.2
unnamed: IC2.13 (O4), K2.5 (-)
unnamed: IC2.12 (O5), K2.6 (-)
unnamed: K2.8, U$23.1
unnamed: K2.4 (S), U$24.2
unnamed: K2.7 (S), U$23.2
unnamed: K1.3, U$22.1
unnamed: K1.2 (O), VCC_RELAIS_101.1
unnamed: LED.K (C), R2.2
unnamed: IC2.9 (CD+), K1.1 (+), K1.10 (+), K2.1 (+), K2.10 (+), R3.1, RELAY_SUPPLY.2
unnamed: K2.2 (O), VCC_RELAIS_103.1
unnamed: K1.9 (O), VCC_RELAIS_100.1
unnamed: K2.9 (O), VCC_RELAIS_102.2
unnamed: U1.1 (SW), U$1.P$2 (2)
unnamed: R6.2, R7.1, U1.4 (FB)
SYS_RESET: 1_ATMEGA328.29 (PC6(/RESET)), C104.1, ISP.5 (RST), R102.2
VCC: C6.1, LOAD_SUPPLY.2, RELAY_SUPPLY.1, VCC.1, VCC_RELAIS_100.2, VCC_RELAIS_101.2, VCC_RELAIS_102.1, VCC_RELAIS_103.2
VIN_1,4V_3.7V: 3.3V_SUPPLY.1, BAT1.PWR@1 (+), BATTTERY_AA.PWR@1 (+), C8.1, CHARGE.2, LOAD_SUPPLY.3, R103.1, U1.3 (EN), U1.6 (VIN), U$1.P$1 (1)
VIN_5V_12V: C1.1, C3.1, FTDI.3, IC1.3 (VI), LOAD_SUPPLY.1, POWER_JACK.1, PUMPED_VCC.2, U$2.4 (VIN), USB.VBUS
VIN_PUMPED: 3.3V_SUPPLY.4, C7.1, LOAD_SUPPLY.4, PUMPED_VCC.1, R6.1, U1.5 (VOUT)
VOUT_3.7V: C2.1, CHARGE.1, U$2.3 (VBAT)

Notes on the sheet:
StepUp Wandler (AA/AAA) (0,35 - Vout) --> 2V, 5,5V (w/o charger!!)
StepDown Wandler (2.7V to 16.0V) --> 3,3V
Battery Charger IN (3,8 - 6V)
Battery Voltage Measurement (Max 9V)

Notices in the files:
parts and their libraries:
SparkFun-Connectors: Licensing: CC v3.0 Share-Alike You are welcome to use this library for commercial purposes.
SparkFun-Retired: Licensing:Creative Commons ShareAlike 4.0 International - https://creativecommons.org/licenses/by-sa/4.0
